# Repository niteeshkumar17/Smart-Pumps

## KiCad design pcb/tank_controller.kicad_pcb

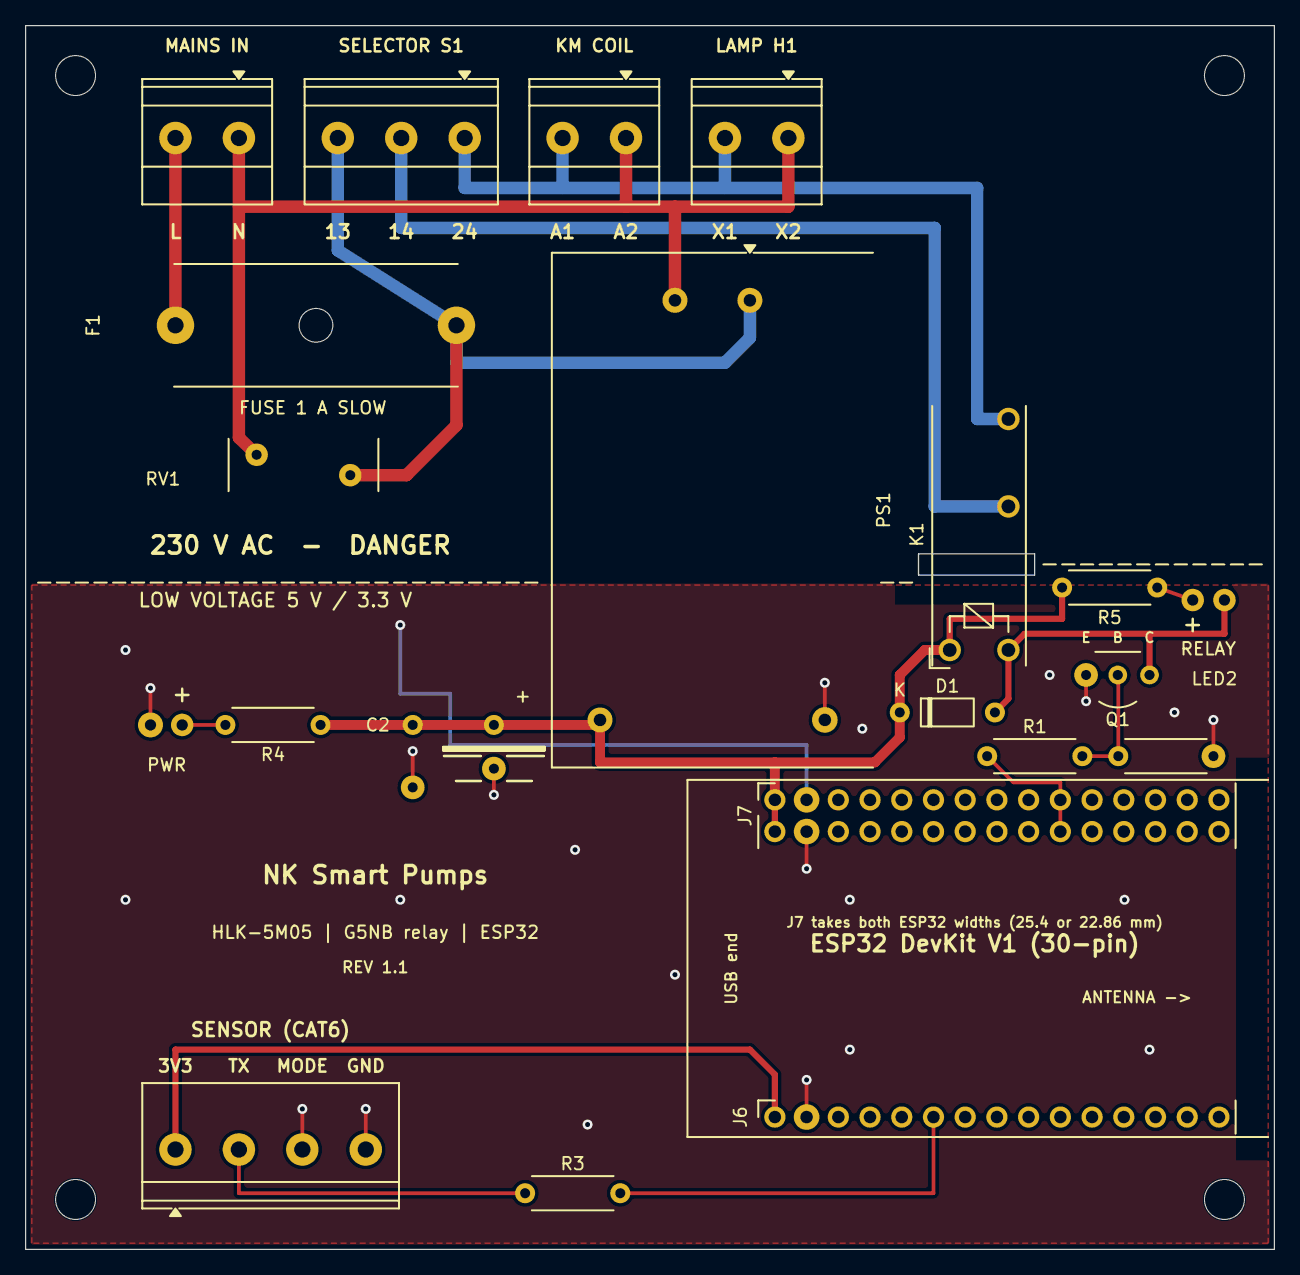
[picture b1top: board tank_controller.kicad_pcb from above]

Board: 2 copper layers, 100.0 x 98.0 mm, 26 parts (0 on the bottom side), 15 nets.

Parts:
C1: 470uF 16V; CP_Radial_D8.0mm_P3.50mm
C2: 100nF; C_Disc_D5.0mm_W2.5mm_P5.00mm
D1: 1N4148; D_DO-35_SOD27_P7.62mm_Horizontal
F1: 1A T; Fuseholder_Cylinder-5x20mm_Schurter_0031_8201_Horizontal_Op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
H1, H2, H3, H4: MountingHole_3.2mm_M3
J1: MAINS IN; TerminalBlock_Phoenix_MKDS-1,5-2-5.08_1x02_P5.08mm_Horizont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
J2: SELECTOR S1; TerminalBlock_Phoenix_MKDS-1,5-3-5.08_1x03_P5.08mm_Horizont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
J3: KM COIL; TerminalBlock_Phoenix_MKDS-1,5-2-5.08_1x02_P5.08mm_Horizont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
J4: LAMP H1; TerminalBlock_Phoenix_MKDS-1,5-2-5.08_1x02_P5.08mm_Horizont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
J5: SENSOR; TerminalBlock_Phoenix_MKDS-1,5-4-5.08_1x04_P5.08mm_Horizont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
J6: ESP32 3V3 side; PinSocket_1x15_P2.54mm_Vertical
J7: ESP32 VIN side; PinSocket_2x15_P2.54mm_Vertical
K1: G5NB-1A-E 5VDC; Relay_SPST_Omron_G5NB
LED1: PWR; LED_D3.0mm
LED2: RELAY; LED_D3.0mm
PS1: HLK-5M05; Converter_ACDC_Hi-Link_HLK-5Mxx
Q1: BC547; TO-92_Inline_Wide
R1, R4, R5: 1k; R_Axial_DIN0207_L6.3mm_D2.5mm_P7.62mm_Horizontal
R2: 10k; R_Axial_DIN0207_L6.3mm_D2.5mm_P7.62mm_Horizontal
R3: 330; R_Axial_DIN0207_L6.3mm_D2.5mm_P7.62mm_Horizontal
RV1: 275VAC; RV_Disc_D12mm_W4.2mm_P7.5mm

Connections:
+3V3: J5.1, J6.1
+5V: C1.1, C2.1, D1.1, J7.1, J7.2, K1.A1, PS1.4, R4.1, R5.1
A1: J2.1, J3.2, J4.2, K1.14
AUTO: J2.2, K1.13
BASE: Q1.2, R1.2, R2.1
COIL_N: D1.2, K1.A2, LED2.1, Q1.1
GND: C1.2, C2.2, J5.3, J5.4, J6.2, J7.3, J7.4, LED1.1, PS1.3, Q1.3, R2.2
LED_PWR: LED1.2, R4.2
LED_RLY: LED2.2, R5.2
L_F: F1.2, J2.3, PS1.1, RV1.1
L_IN: F1.1, J1.2
N: J1.1, J3.1, J4.1, PS1.2, RV1.2
RLY: J7.19, J7.20, R1.1
RX2: J6.6, R3.2
SENS_TX: J5.2, R3.1

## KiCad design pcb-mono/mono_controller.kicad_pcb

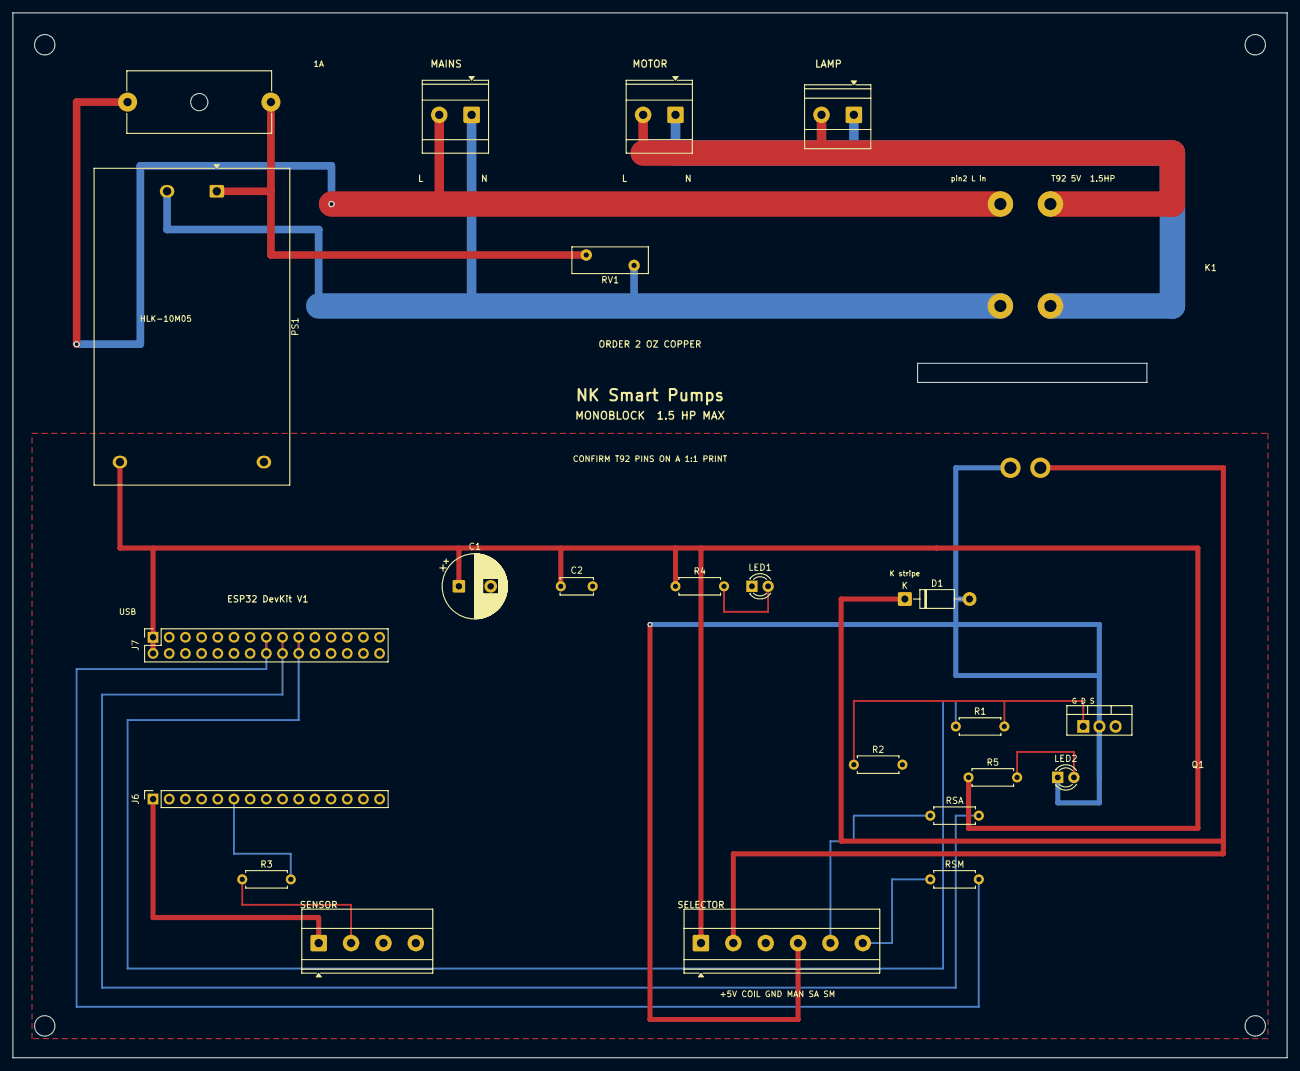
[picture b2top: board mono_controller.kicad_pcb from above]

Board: 2 copper layers, 200.0 x 164.0 mm, 28 parts (0 on the bottom side), 20 nets.

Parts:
C1: 1000uF 16V; CP_Radial_D10.0mm_P5.00mm
C2: 100nF; C_Disc_D5.0mm_W2.5mm_P5.00mm
D1: 1N4007; D_DO-41_SOD81_P10.16mm_Horizontal
F1: 1A T; Fuseholder_Cylinder-5x20mm_Schurter_0031_8201_Horizontal_Op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
H1, H2, H3, H4: MountingHole_3.2mm_M3
J1: MAINS; TerminalBlock_Phoenix_MKDS-3-2-5.08_1x02_P5.08mm_Horizontal
J2: MOTOR; TerminalBlock_Phoenix_MKDS-3-2-5.08_1x02_P5.08mm_Horizontal
J3: LAMP; TerminalBlock_Phoenix_MKDS-1,5-2-5.08_1x02_P5.08mm_Horizont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
J4: SELECTOR; TerminalBlock_Phoenix_MKDS-1,5-6-5.08_1x06_P5.08mm_Horizont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
J5: SENSOR; TerminalBlock_Phoenix_MKDS-1,5-4-5.08_1x04_P5.08mm_Horizont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
J6: ESP32 3V3 side; PinSocket_1x15_P2.54mm_Vertical
J7: ESP32 VIN side; PinSocket_2x15_P2.54mm_Vertical
K1: T92P7D12-5; Relay_TE_T92
LED1: PWR; LED_D3.0mm
LED2: RELAY; LED_D3.0mm
PS1: HLK-10M05; Converter_ACDC_Hi-Link_HLK-10Mxx
Q1: IRLZ44N; TO-220-3_Vertical
R1: 100; R_Axial_DIN0207_L6.3mm_D2.5mm_P7.62mm_Horizontal
R2: 100k; R_Axial_DIN0207_L6.3mm_D2.5mm_P7.62mm_Horizontal
R3: 330; R_Axial_DIN0207_L6.3mm_D2.5mm_P7.62mm_Horizontal
R4, R5: 1k; R_Axial_DIN0207_L6.3mm_D2.5mm_P7.62mm_Horizontal
RSA: 1k; R_Axial_DIN0207_L6.3mm_D2.5mm_P7.62mm_Horizontal
RSM: 1k; R_Axial_DIN0207_L6.3mm_D2.5mm_P7.62mm_Horizontal
RV1: 275VAC; RV_Disc_D12mm_W4.2mm_P7.5mm

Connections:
+3V3: J5.1, J6.1
+5V: C1.1, C2.1, J4.1, J7.1, J7.2, PS1.4, R4.1, R5.1
COIL: D1.1, J4.2, K1.1
DRAIN: D1.2, J4.4, K1.0, LED2.1, Q1.2
GATE: Q1.1, R1.2, R2.1
GND: C1.2, C2.2, J4.3, J5.3, J5.4, J6.2, J7.3, J7.4, LED1.1, PS1.3, Q1.3, R2.2
LED_PWR: LED1.2, R4.2
LED_RLY: LED2.2, R5.2
L_F: F1.2, PS1.1, RV1.1
L_IN: F1.1, J1.2, K1.2
L_OUT: J2.2, J3.2, K1.4
N_IN: J1.1, K1.6, PS1.2, RV1.2
N_OUT: J2.1, J3.1, K1.8
RLY: J7.19, J7.20, R1.1
RX2: J6.6, R3.2
SA: J4.5, RSA.1
SEL_A: J7.17, J7.18, RSA.2
SEL_M: J7.15, J7.16, RSM.2
SENS_TX: J5.2, R3.1
SM: J4.6, RSM.1

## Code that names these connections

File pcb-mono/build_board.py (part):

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track("N_OUT", NECK_W, pcbnew.B_Cu, "J3.1", (132, 22))
track("N_OUT", MOTOR_W, pcbnew.B_Cu, (104, 22), (182, 22), (182, 46), "K1.8")

# Coil driver. IRLZ44N, front view, pins left to right: gate, drain, source.
place("Q1", "Package_TO_SOT_THT", "TO-220-3_Vertical", 168, 112, 0, "IRLZ44N",
      {1: "GATE", 2: "DRAIN", 3: "GND"})
fps["Q1"].Reference().SetPosition(P(186, 118))
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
